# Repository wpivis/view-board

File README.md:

# view-board

For our very own [AnyPixel.js](http://googlecreativelab.github.io/anypixel/) board
=========

## Architecture

Project uses a Teensy 3.2 board to control the WS2812 LED strip and buttons, using serial data to communicate. 

## Install

To install the library, simply type this into your nearest console: 
```js
npm install nopixel
```

At this point, depending on the distribution, you may note that your computer is slightly unhappy. This is due to the fact that `nopixel` relies on `serialport` to get access to, well, the serial port. `serialport` however, relies on `node-gyp` which is notoriously hard to build. Therefore I recommend you go to https://github.com/nodejs/node-gyp#installation for your troubleshooting needs.

If installation of `nopixel` still fails, please run 
```js
npm install serialport
```

## Usage

- Flash the firmware found in `firmware/arduino_firmware` to the Teensy. For this you will need to install [Teensyduino](https://www.pjrc.com/teensy/teensyduino.html)
- Create a `config.json` following this template
	```json
	[{
		"comPort": "/name/of/comPort",
		"baudRate": "BAUD_RATE"
	}]
	```
- Run `node app.js` for the example app

### Canvas support

This module supports `node-canvas`. Simply create a 7x7 canvas, then export it to the board using 
```js
	var data = ctx.getImageData(0,0,7,7);
	nopixel.fromCanvas(data);
	nopixel.update();
```
For a working example, look into examples/ConnectFour

### API

#### Events

All nopixel events, with the exception of `ready`, sends back an object `eventDetail` with the coordinates of the button press in the form of 

```js
var eventDetail = {
	x: 	X-coordinate of the button press (0-6),
	y: 	Y-coordinate of the button press (0-6),
	index: 	Index of the button press (0-48)
}
```

#### `.on('ready')`

Emits when established a connection with the board. Throws an error otherwise.

#### `.on('clicked')`

Emits when a button is pressed quickly - aka 'onButtonDown'. Pass an `eventDetail` object.

#### `.on('pressed')`

Emits when a button is held down. Pass an `eventDetail` object.

#### `.on('released')`

Emits when a button is released - aka 'onButtonUp'. Pass an `eventDetail` object.

#### `.on('idle')`

Emits the default state, when nothing is happening. Pass an `eventDetail` object.

#### Functions

#### `.setPixel()`

```js
nopixel.setPixel(x, y, colorObj)
```

Where x,y denotes the coordinates on the board (0-6), and colorString is a valid `tinyColor2` object. Examples includes string input (`"black"`, `"f0f0f6"`, `"rgb (255, 0, 0)"`, `"hsla(0, 100%, 50%, .5)"`), or RGB/RGBA/HSL/HSLA/HSV/HSVA objects (`{ h: 0, s: 1, l: .5 }`)

#### `.update()`

```js
nopixel.update()
```

aka `render`. Pushes and set all changes to LEDs at the same time. This prevents multiple refresh calls to the board and saves clock cycles.

#### `.clear()`

```js
nopixel.clear()
```

Sets all pixels to black, essentially turning them off.

#### `.fromCanvas()`

```js
nopixel.fromCanvas(canvasBuffer)
```

`node-canvas` integration. Takes in a Canvas buffer and send it to the LEDs.

#### `.write()`

```js
nopixel.write(string, colorObj, scrollSpeed)
```

One of the two text writing functions. `.write()` is used for anything more than a single letter, and will scroll the text in `string`, in color `colorObj`, looping indefinitely at a speed (delay between updates) `scrollSpeed`. 

Passes back a `setInterval` object. To stop scrolling use the built-in `clearInterval()`.

For more information check out the `TextDisplay` example.

#### `.writeLetter()`

```js
nopixel.writeLetter(letter, colorObj, x, y)
```

The other text writing function. As opposed to `.write()`, `.writeLetter()` as the name suggests, only prints one `letter` at a time, in color `colorObj`, starting at coordinates `x` `y`.

Fonts configuration is stored in `letters.json` as two-dimentional arrays, with 1 as filled, and 2 as unfilled - feel free to change them as you see fit.

### Opcodes

See `commands.md`

## Future work

[ ] Emulator

[ ] Make an even bigger one!

[ ] Use pre-wired WS2812 instead of manually soldering wires

[ ] Utility buttons?

[ ] Flushed USB port

[ ] getPixelData() function

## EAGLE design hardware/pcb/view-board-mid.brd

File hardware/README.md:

# Hardware Sources

In here you will find sources for the laser-cut case and the (non-existent) PCB

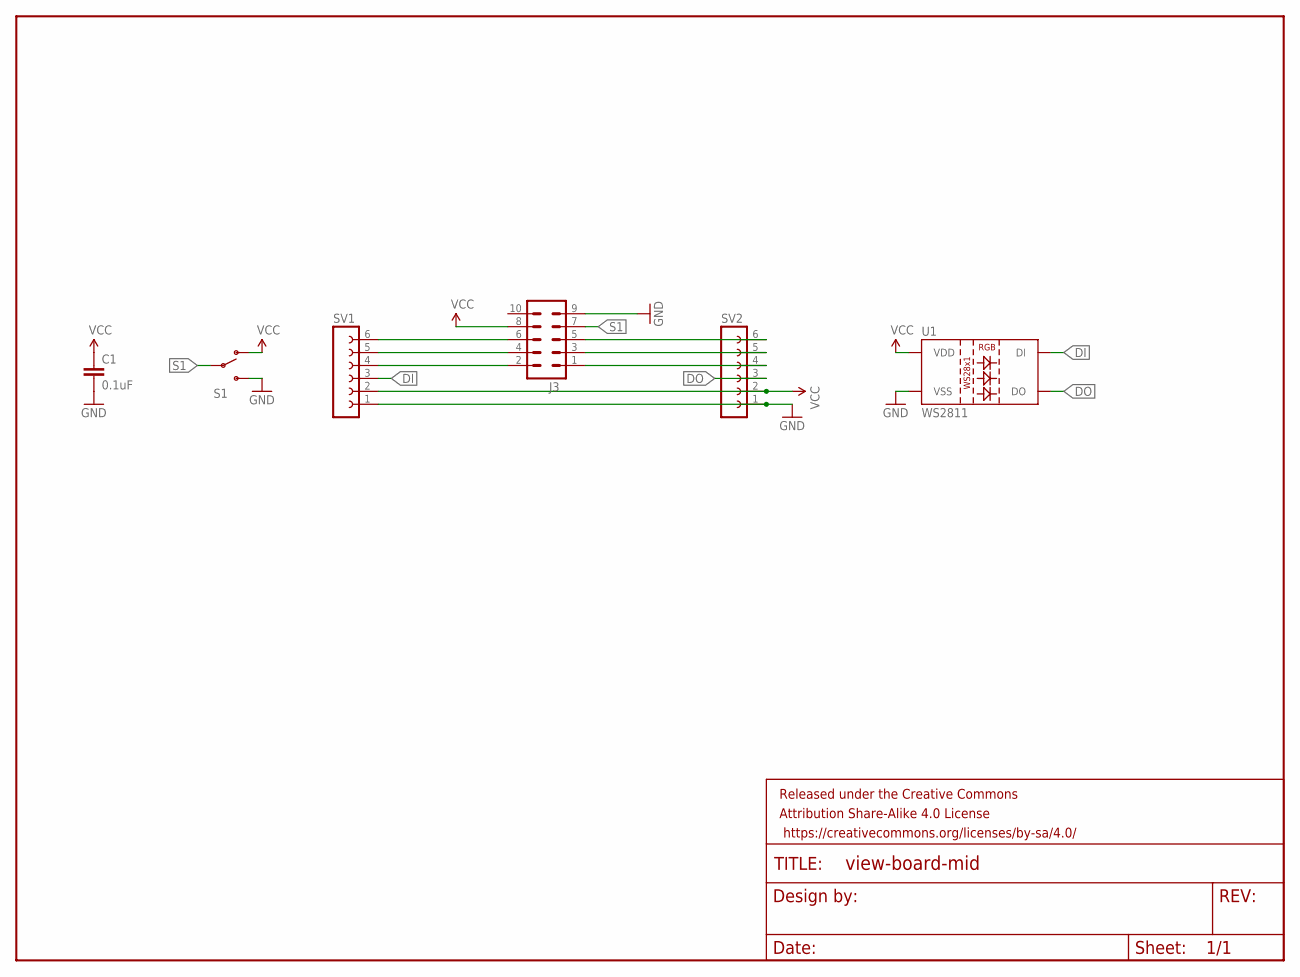
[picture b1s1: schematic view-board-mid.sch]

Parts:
C1: 0.1uF; 0805
FRAME1: FRAME-LETTER; CREATIVE_COMMONS
J3: M05X2SHD; 2X5-SHROUDED
S1: SWITCH-SPDTPTH; SWITCH-SPDT
SV1, SV2: FE06-1; FE06
U1: WS2811; LED-TRICOLOR-5050-IC

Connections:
DI: SV1.3, U1.2 (DI)
DO: SV2.3, U1.1 (DO)
GND: C1.2, J3.9, S1.3 (S), SV1.1, SV2.1, U1.6 (VSS)
unnamed: J3.2, SV1.4
unnamed: J3.1, SV2.4
unnamed: J3.3, SV2.5
unnamed: J3.4, SV1.5
unnamed: J3.6, SV1.6
unnamed: J3.5, SV2.6
S1: J3.7, S1.2
VCC: C1.1, J3.8, S1.1 (O), SV1.2, SV2.2, U1.3 (VDD), U1.5 (VDD)

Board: 2 copper layers, 7 parts (0 on the bottom side), 11 nets, no tracks yet.

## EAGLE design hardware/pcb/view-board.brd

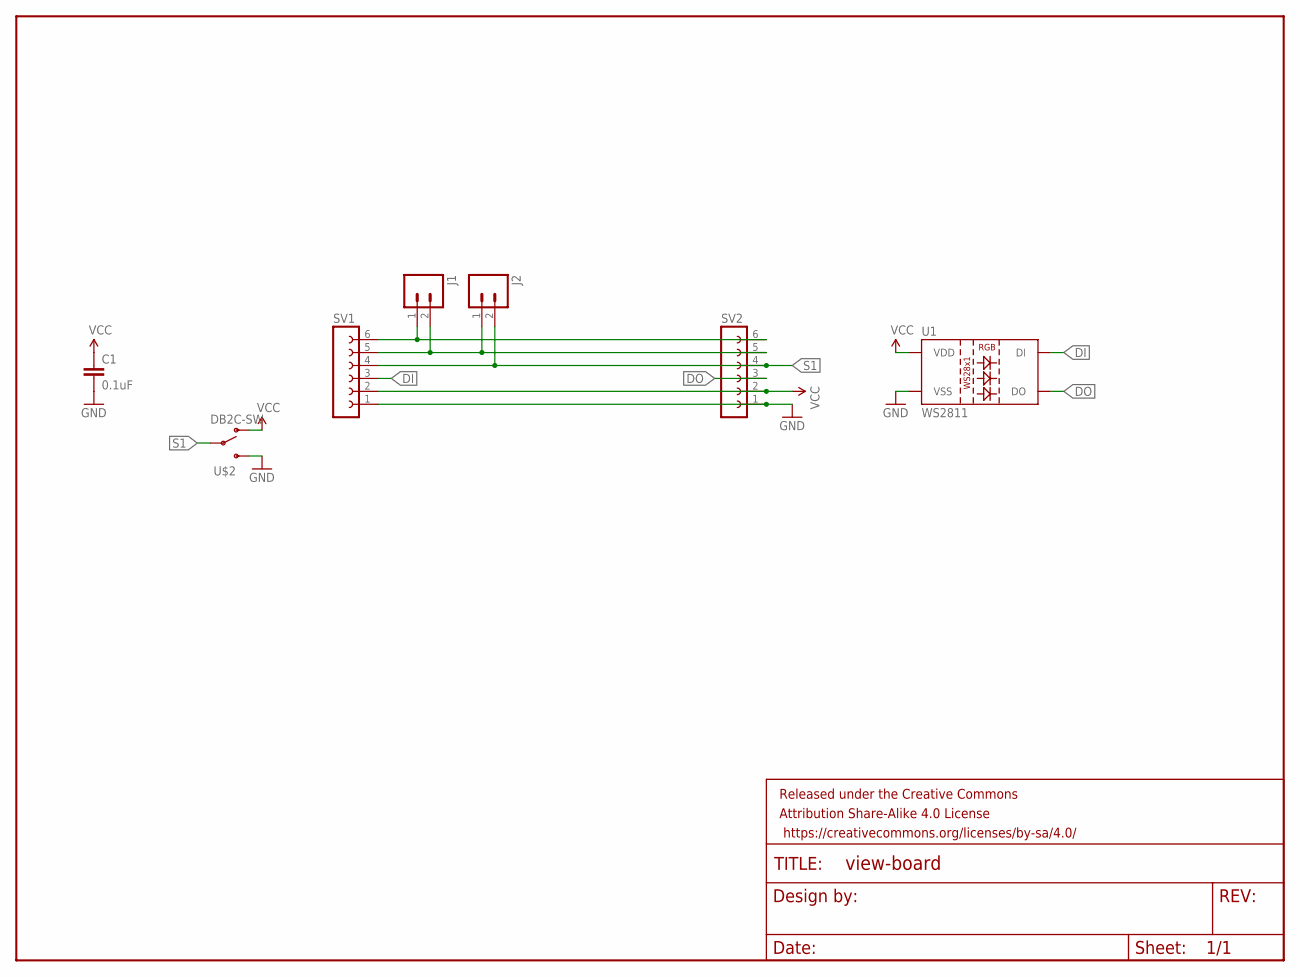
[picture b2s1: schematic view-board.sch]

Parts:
C1: 0.1uF; 0805
FRAME1: FRAME-LETTER; CREATIVE_COMMONS
J1, J2: M02LOCK; 1X02_LOCK
SV1, SV2: FE06-1; FE06
U1: WS2811; LED-TRICOLOR-5050-IC
U$2: DB2C-SW; CHERRY-DB2C

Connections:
DI: SV1.3, U1.2 (DI)
DO: SV2.3, U1.1 (DO)
GND: C1.2, SV1.1, SV2.1, U1.6 (VSS), U$2.3 (S)
unnamed: J1.1, SV1.6, SV2.6
unnamed: J1.2, J2.1, SV1.5, SV2.5
S1: J2.2, SV1.4, SV2.4, U$2.2
VCC: C1.1, SV1.2, SV2.2, U1.3 (VDD), U1.5 (VDD), U$2.1 (O)

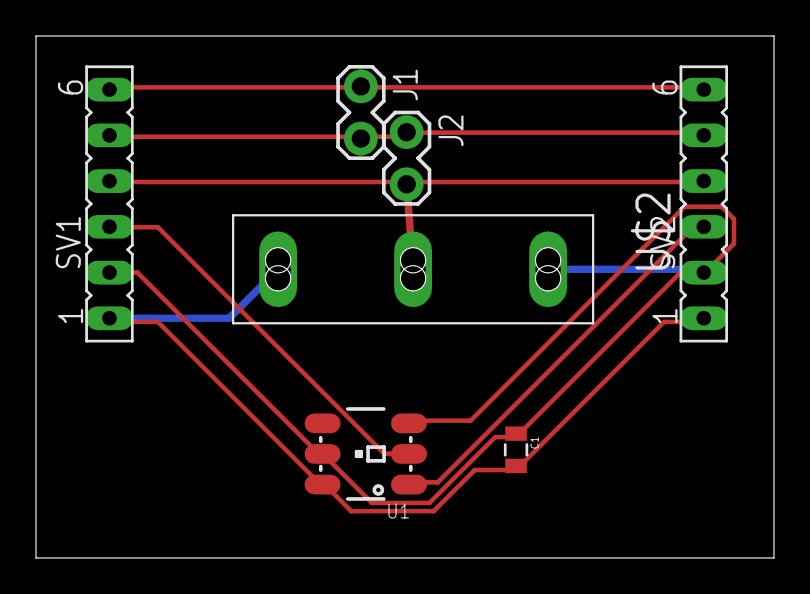
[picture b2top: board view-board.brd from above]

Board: 2 copper layers, 41.0 x 29.0 mm, 8 parts (0 on the bottom side), 7 nets.

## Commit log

2016-06-17 First hacky bits
2016-06-20 Hackiest way ever - working square floats for demo board
2016-06-20 Board selection on mouse down
2016-06-21 Addressibility added
2016-06-23 Module json added, cleaned up backend
2016-06-24 Configured modular structure
2016-06-27 Config file for review
2016-06-27 Config file for review
    Changes to be committed:
    new file: nopixel/config.json
    modified: nopixel/index.js
2016-06-27 Reading config file works
2016-06-27 Fixed module structure
2016-06-29 Changed button structure
2017-07-20 Old stuff. Prepare for major rewrite.
2017-08-04 Prototype working unter ./test/
2017-08-04 Rewrote NoPixel.JS to work with new firmware
2017-08-05 Implemented Game of Life as an example
2017-08-05 Added Update opcode
2017-08-05 Fixed cell color
2017-08-05 Fixed blocking statement in firmware
2017-08-06 Finishing up Game of life, updated main app.js
2017-08-07 Started other examples
2017-08-10 More Opcodes
2017-08-10 Removed node_modules/ from examples
2017-08-10 Reworked frame setter, increased buffer
2017-08-10 Fixed fromCanvas
2017-08-11 Still working
2017-08-11 Removed old stuff. Rewrote README.
2017-08-11 More readme
2017-08-12 Fixed use strict
2017-08-13 Updated mechanical design, added standoffs and usb adapter
2017-08-14 Room-light controls
2017-08-14 Fixed button holder
2019-11-16 Multiple factoring in both library, software and example app(s)
    This is a big commit that I should've done sooner.
    Software-wise, I went through the `nopixel` library and cleaned up the code, added constant for opcodes instead of magic numbers, wrote more descriptive console log and added a `ready` event that wil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
    Hardware wise, I swapped a couple of pins on the Teensy board, mainly
    because the old Teensy 2.0 board burned out and I had to replace it with
    the newer Teensy 3.2. Expect more pin changes in the future. Also I
    don't understand why Arduino straight up replaced the file instead of
2019-11-17 Finished HelloWorld example
    Fixed a quick bug that stems from shoddy opcode decision. Added a hello
    world example that randomizes colors on the board and independently
    changes them.
2019-11-17 Added pixel font, example and refactored errorhandling
    Implemented a small pixel font - around 3x6 to 5x6 in size. Based on
    https://robey.lag.net/2010/01/23/tiny-monospace-font.html
    I also refactored error handling, instead of console.log, errors are now
    thrown properly.
2019-11-18 Minor QoL improvements to TextDisplay, quick 'ready' event fix and README update
    'ready' event used to be hardcoded to emit 1 millisecond after we
    initiate connection. This, in every single aspects, was not a good idea.
    But it worked.
    After actually bothering to look at the node `serialport` library, I
    added a passthrough 'read' event without the need for hardcoding.
    You're welcome, past me.
2019-11-18 Bump canvas from 1.6.6 to 1.6.10 in /examples/ConnectFour
    Bumps [canvas](https://github.com/Automattic/node-canvas) from 1.6.6 to 1.6.10.
    - [Release notes](https://github.com/Automattic/node-canvas/releases)
    - [Changelog](https://github.com/Automattic/node-canvas/blob/master/CHANGELOG.md)
    - [Commits](https://github.com/Automattic/node-canvas/compare/v1.6.6...v1.6.10)
2019-11-21 Updated README.md
    Wrote a proper description for the API.
2021-05-08 Bump canvas from 1.6.10 to 1.6.11 in /examples/ConnectFour
    Bumps [canvas](https://github.com/Automattic/node-canvas) from 1.6.10 to 1.6.11.
    - [Release notes](https://github.com/Automattic/node-canvas/releases)
    - [Changelog](https://github.com/Automattic/node-canvas/blob/master/CHANGELOG.md)
    - [Commits](https://github.com/Automattic/node-canvas/compare/v1.6.10...v1.6.11)

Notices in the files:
parts and their libraries:
SparkFun-Capacitors: Licensing: Creative Commons ShareAlike 4.0 International - https://creativecommons.org/licenses/by-sa/4.0
SparkFun-Aesthetics: Released under the Creative Commons Attribution Share-Alike 4.0 License
SparkFun-Aesthetics: https://creativecommons.org/licenses/by-sa/4.0
